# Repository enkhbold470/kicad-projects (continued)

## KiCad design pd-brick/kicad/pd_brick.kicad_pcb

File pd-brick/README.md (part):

# PD Brick

A USB-C Power Delivery bench supply: STUSB4500 sink, LM5176 buck-boost, 1.2-22 V set over I2C by an ESP32-S3.

| Layers | Size | Parts | Nets | Connections routed | Vias | ERC errors | DRC errors / unconnected / parity |
|---|---|---|---|---|---|---|---|
| 4 | 100 x 80 mm | 120 | 71 | 283 -> 0 open | 208 | 0 | 0 / 0 / 0 |

**Not fabricated, assembled or powered.** Every number on this page is measured by KiCad 10 on the files in this folder; the full measurements are in [`report.json`](report.json).

| | |
|---|---|
| KiCad project | [`kicad/`](kicad/) |
| Gerbers, BOM, CPL, STEP, schematic PDF | [`fab/`](fab/) |
| Renders | [top](media/top.png), [bottom](media/bottom.png) |
| Design process, every step as KiCad rendered it | [`media/design-process.mp4`](media/design-process.mp4) |

PD Brick is a USB-C Power Delivery programmable bench supply with a 1.2-22 V output. It was designed with the HeyPCB method on KiCad 10. A headless pipeline (KiCad 10.0.6, Freerouting 2.4.1) took the brief in `board.json` through schematic, placement, routing, pours, DRC and fab outputs.

**This board has not been fabricated, assembled or powered. There is no firmware.** On the final run it passes these checks:

- ERC and the netlist round trip;
- routing at 0 open;
- DRC with 0 errors, 0 unconnected and 0 schematic-parity rows;
- DFM with 0 errors.

The fab gate is ready. Everything under "Check before ordering" is a datasheet calculation or a layout measurement, not a bench result.

## What it is

- **Input:** USB-C, USB PD 3.0 sink up to 20 V (ST STUSB4500). The controller closes an AOD4185 P-FET between the receptacle and the power stage. There is a 24 V TVS on the receptacle.
- **Converter:** TI LM5176 4-switch buck-boost at about 390 kHz, with:
  - four TI CSD18563Q5A 60 V FETs;
  - a Coilcraft XAL7070 4.7 uH / 15.2 A inductor;
  - a 10 mOhm low-side current-sense resistor;
  - 220 uF + 4 x 10 uF on each side.

  The output is about 1.2-22 V.
- **Setpoint:** a Microchip MCP4725 12-bit I2C DAC injects into the LM5176 feedback node through 15k. A higher code gives a lower voltage.
- **Monitor:** a TI INA228 (20-bit V / I / power / energy) on a 10 mOhm high-side output shunt. It shares the LM5176's average-current-limit filter on the same shunt (50 mV, about 5 A).
- **Output enable:** one CSD18563Q5A high-side N-FET. Its gate is pulled up from a 25.6 V rail made by an MT3608 boost, Vgs is clamped at 12 V, and a 2N7002 pulls the gate down. The output is off from reset.
- **Output:** Phoenix MKDS 1,5/2-5,08 screw terminal (17.5 A), with an SMBJ24A TVS and 1 uF across it.
- **MCU:** ESP32-S3-WROOM-1-N8R8, from the HeyPCB block `esp32_s3_minimal`:
  - Wi-Fi for remote control;
  - native USB on the same USB-C port (USBLC6-2SC6 on D+/D-, referenced to 3V3);
  - BOOT and RESET buttons.
- **3.3 V:** Diodes AP63203 buck from VBUS (3.8-32 V in). An LDO would burn up to 8 W from a 20 V contract.
- **UI:**
  - a 1x4 0.1" header for a 1.3" I2C OLED (GND, VCC, SCL, SDA), with the bus pull-ups;
  - an Alps EC11E push-button encoder;
  - PWR, PD and OUT LEDs.
- **Board:** 100 x 80 mm, four M3 holes, 4 layers:
  - F.Cu;
  - In1, a GND plane;
  - In2, routing with a 3V3 pour;
  - B.Cu.

### Chip substitutions

| Asked for | Fitted | Why |
|---|---|---|
| TPS55289 (or similar) I2C buck-boost | LM5176 controller + 4 x CSD18563Q5A + MCP4725 DAC | KiCad 10 has no TPS55289 (or TPS552xx) symbol, and the live JLC lookup returned no TPS55289 row. The LM5176 (`Regulator_Switching:LM5176PWP`, LCSC C442493) has no I2C, so the DAC programs its FB node. |
| STUSB4500, AP33772 or CH224K | STUSB4500 | All three have KiCad 10 symbols. The AP33772 returned no JLC row. The CH224K is pin-strapped, with no I2C. The STUSB4500 (C2678061) renegotiates over I2C at 0x28. |
| INA228 (or INA226) | INA228 | `Sensor_Energy:INA228`, C2887910. |
| Load switch or MOSFET | one CSD18563Q5A high-side N-FET + MT3608 gate rail | No KiCad 10 load switch covers 1-22 V at several amps. A P-FET cannot turn on at a 1 V output. A low-side switch is bypassed by any second ground (a scope, or a USB-powered load). |
| (VBUS switch for VBUS_EN_SNK) | AOD4185 on the generic `Transistor_FET:Q_PMOS_GDS` symbol | KiCad 10 has no AOD4185 symbol. Q_PMOS_GDS (1 G, 2 D, 3 S) is this part's TO-252 land (tab = drain). |
| (power FETs) | CSD18563Q5A, 5 x 6 mm | The 3.3 x 3.3 mm CSD18543Q3A was tried first. Its KiCad VSON land puts the gate pad 0.14 mm from a source pad, so DRC fails at 0.2 mm on the footprint itself. |

### How it is wired

```
USB-C -VBUS-> AOD4185 (STUSB4500 VBUS_EN_SNK) -VIN-> LM5176 buck-boost -VOUT-> 10 mOhm shunt -VOUT_SH-> N-FET -OUT_P-> terminal
   |                                                ^ FB <- 15k <- MCP4725 (I2C)   |  ISNS 100R/100R/1uF -> LM5176 + INA228
   +-VBUS-> AP63203 -3V3-> ESP32-S3, STUSB4500 I2C side, INA228, DAC, OLED, encoder          gate <- 1M <- 25.6 V (MT3608 off VIN)
```

- **Setting the output.** FB has 100k from VOUT and 4.7k to GND, and the DAC drives FB through 15k:

  VOUT = 0.8 V x (1 + 100/4.7 + 100/15) - VDAC x 100/15

  That is about 23.2 V at code 0 and 1.2 V at full scale. Firmware clamps the code to 1.2-22 V.
- **Order at power-up.**
  1. The STUSB4500 closes the VBUS switch at attach.
  2. The LM5176 stays off: EN has a 100k pull-down.
  3. The output stays off: OUT_OFF has a 22k pull-up.
  4. Firmware writes the DAC, sets BB_EN high, then pulls OUT_OFF low.
- **Wide power nets.** No 1.2 mm power track lands on an IC pin. On the routed board, the seven power-path nets reach only FETs, the inductor, passives, the TVS, the zener and the terminal. Every IC pin on a power net hangs off it through a resistor, placed at the power node (an `at` target in the brief):
  - LM5176 VIN, VISNS, VOSNS, SW1/SW2, CS/CSG and ISNS;
  - STUSB4500 VDD;
  - INA228 VBUS;
  - MT3608 IN.
- **I2C** (IO38 SDA, IO39 SCL, 4.7k pull-ups):
  - STUSB4500 at 0x28;
  - INA228 at 0x40;
  - MCP4725 at 0x60;
  - the OLED module at its own address.
- **ESP32-S3 pins.** All GPIOs are on the module's right column and bottom row, which face the board:

  | Pin | Function |
  |---|---|
  | IO42 / IO41 / IO40 | encoder A / B / switch |
  | IO1 / IO2 | PD / OUT LEDs |
  | IO10 | PD_RST |
  | IO11 | PD_ALERT |
  | IO12 | BB_EN |
  | IO14 | OUT_OFF |
  | IO19 / IO20 | USB D- / D+ |
  | IO0 | BOOT |

  The LM5176 PGOOD, the INA228 ALERT and a VIN divider were cut to shorten routing; the INA228 and STUSB4500 report the same information over I2C.

## Measured (full run of 2026-10-01)

Gate numbers come from `report.json`. Rows marked "on the board" were measured on `kicad/pd_brick.kicad_pcb` with KiCad's Python (`pcbnew`, read-only scripts). Current ratings use `ipc2221_amps` from the pipeline (IPC-2221, 1 oz outer, 0.5 oz inner). A path's rating is the total current at which its busiest segment reaches its own rating at a 20 C rise. The share each segment carries comes from solving the net's copper as a resistor network, with the source pads tied (ideal contacts).

| Gate | Result |
|---|---|
| Composition | 18 block instances, 16 distinct blocks (11 written for this board, 5 reused) → 120 footprints, 71 nets |
| Part binding | 116 of 116 BOM parts bound to a pinned LCSC table, 0 unsourced, 0 conflicts. H1-H4 are drilled M3 holes, kept out of the BOM. 23 distinct Extended parts, about $69 in JLC loading fees. 1 warning: the 10k 0603 R9 (C25804, the ESP32 EN pull-up) had 0 stock at its 2026-06-23 snapshot |
| ERC (`kicad-cli sch erc --severity-all`) | 0 errors, 0 warnings |
| Netlist round trip | identical, 71 nets |
| Freerouting, rung 1, fanout on (kept) | 283 → **0 open** in 160.9 s, with no last-mile help. DRC score 0, 73 vias |
| Freerouting, rung 1, fanout off (for comparison) | 283 → 1 open (VOUT, R17.1 to C29.1) in 38.4 s. The last-mile router found no path, so this rung was not kept |
| Copper | 908 tracks, 73 routing vias, 2856.2 mm of track (F.Cu 1624.4, In2 1030.5, B.Cu 201.3). No segment was widened, kept narrow or raised: every segment is at its class width (also checked on the board) |
| VBUS input (on the board) | 0.6 mm, all on F.Cu, no vias. Each receptacle VBUS pad pair has its own track to Q1's source pad: 8.6 mm from A4/B9 and 7.5 mm from A9/B4. No segment is shared; the two tracks meet only inside the source pad. They split the current 45 / 55. Path rating **4.07 A** at a 20 C rise (3.0 A at 10 C) |
| Power path (on the board) | VIN, BB_SW1, BB_SW2, BB_CS, VOUT, VOUT_SH and OUT_P run only on F.Cu at 1.2 mm, with no vias and no necks. OUT_P's branch to the output TVS is F.Cu too. VIN from Q1 to the buck high-side FET, and the output path (VOUT, VOUT_SH, OUT_P) to the terminal, each rate **3.70 A** at a 20 C rise |
| 3.3 V buck (on the board) | Switch node 0.8 mm on F.Cu, no vias: 1.6 mm from the AP63203's SW pin to the inductor pad, 5.1 mm with the branch to the bootstrap cap. Rated **2.76 A** at a 20 C rise. 3V3 is 0.3 mm everywhere (271.5 mm: F.Cu 87.9, In2 169.1, B.Cu 14.5, 10 vias), with the In2 3V3 pour around it |
| Pours (only after a measured 0 open) | GND on F.Cu, B.Cu and In1; 3V3 on In2. 144 stitching vias, 0 island-repair vias, still 0 open. 217 vias in all |
| DRC (`kicad-cli pcb drc --severity-all --schematic-parity`) | fresh: 0 errors, 3 warnings, 0 unconnected, 0 parity |
| DFM (`jlcpcb_4layer`) | 0 errors, 1 warning: 338 stock-footprint silk strokes at 0.12 mm, which the fab prints at its 0.15 mm minimum |
| Fab gate | **ready**, no blockers. Outputs: gerbers for four copper layers (the gerber job says 4 layers, 1.6 mm), drill, BOM, JLC placement file (8 rotations corrected), position file, schematic PDF, STEP |

- **The 3 DRC warnings** are `lib_footprint_mismatch` on three parts: the USB-C receptacle (J1), the terminal (J2) and the ESP32-S3 module (U4).
  - Silk is clipped at the board edge, so each has fewer silk shapes than its library copy: 2 of 5, 6 of 9 and 4 of 8 (on the board).
  - J1's shield pads are also set to join the GND pour solid.
- **Hole spacing.** The closest via holes on different nets are 0.53 mm apart (I2C_SCL and J1_PD_DISCH), against the 0.5 mm board rule (on the board).
- **Silk** (from `report.json`, texts read back on the board).
  - All 7 words fit: PD IN, PWR, PD, OUT, BOOT, RST and SET.
  - OUT+ and OUT- sit beside the terminal's two pins.
  - The OLED header's pin names (GND, VCC, SCL, SDA) are printed on both faces: 8 labels.
  - All 4 back title lines fit.
  - 84 designators were seated and 28 hidden; parts that carry a word hide theirs. 10 silk shapes were clipped at the board edge, and 9 stitching vias gave way to text.
- **Media.** Render and video ran in the same full run as the gates. The design-process video (`media/design-process.mp4`) is 168.6 s long (ffprobe on the run's own MP4), made from 253 stills. It ends on the fab card.
- **Repeatability.** Two full runs of the final brief (one `--no-media`, then the full run with media) routed identically: 908 tracks, 73 vias, 2856.2 mm, and the same VBUS feeds and split. A brief change is a new sample, though. Adding one more F.Cu keep-out (under the receptacle body) routed the VBUS feeds into one shared 0.6 mm track again (see below). After the final run, only `why` texts in `board.json` were corrected; nothing they feed changed.

### What changed along the way (each measured on this board)

- **The schematic packer.** It could not fit one 52-part buck-boost block on A1 (993 mm wide), so the block was split into a controller block and a power-stage block.
- **Sense resistors at the power nodes.** Left to the shelf placer, they landed under the controller. Every 1.5 mm power track then had to cross the controller's satellites, and Freerouting stalled at 22 unrouted.
- **The output switch.** A back-to-back (source-to-source) pair was tried first. With the S-S-S-G pinout, one gate always sits across the wide source-to-source track, and that gate net was left open in four of six rebuilds. The board now uses a single FET (see "Check before ordering").
- **An early 0-open route** ran the output (OUT_P) through one via and 17.9 mm of In2: about 1.3 A on 0.5 oz inner copper. Placing the terminal pin level with the FET drain moved it to F.Cu. On the final board, OUT_P has no inner-layer copper at all.
- **The VBUS input.** On the previous build, the last 7.8 mm of VBUS into Q1 was a single 0.6 mm track carrying all the input current. That is 2.24 A at a 20 C rise, and about a 39 C rise at 3 A. Freerouting had left the A9/B4 pad pair unrouted because its CC2 fan-out via sat too close to that pad's exit. The last-mile router then joined that pair onto the other pair's track. A wider class cannot help: the receptacle's VBUS pads are 0.6 mm wide, 0.2 mm from the GND pad beside them, and Freerouting runs with neckdown off. What fixed it, over four `--no-media` runs:
  - Q1 is locked with its source pad level with the middle of the two VBUS pad pairs, and its gate network is pinned above it, out of the way.
  - The VBUS class clearance went from 0.2 mm to 0.15 mm, the board's. At 0.2 mm, a 0.6 mm track had a 0.05 mm window to leave the A4/B9 pad, and Freerouting reported `J1-B9 -> J1-A9` unrouted.
  - `board.keepouts` add:
    - an F.Cu track ban above the A4/B9 feed and a via ban along it;
    - an F.Cu track ban box and wedge between the two feeds, up to the source pad;
    - a via guard beside the CC2 pad.
  - The first try used via-free corridors along both feeds. Both pairs still merged into one 6.2 mm detour. The width floor also kept two 0.45 mm VBUS stubs that Freerouting laid at the pads narrow, because it never widens a segment whose midpoint lies in a via keep-out.
- **The 3.3 V buck.** Before, the switch node was a 0.15 mm track (about 0.8 A), and the output caps sat on the far side of the IC from the inductor. Now the IC, inductor and four caps are locked as one cell:
  - the input cap sits under the IN and GND pins;
  - the inductor sits against the SW pin;
  - the bootstrap cap sits above BST;
  - both output caps sit under the inductor's 3V3 pad, with their GND pads beside the input cap's.

  The switch node has its own 0.8 mm class and 3V3 a 0.3 mm class.
- **Silk.** On the previous build, 4 of 7 words fit (BOOT, RST and the OUT LED's word did not), the terminal had no + / - mark, and 0 of 8 OLED pin labels fit. The fixes were all in the brief:
  - **BOOT and RESET.** The module's courtyard box, antenna keep-out included, spans x -4 to 44 mm and y down to 20.3 mm. The silk stage keeps words off every courtyard box, so the two buttons moved out of it.
  - **LEDs.** They are spaced 3.75 mm apart, each with its resistor below it.
  - **OLED header.** It now stands vertical, so its pin names land beside the pins.
  - **Terminal marks.** They come from a `silk.switches` entry. `silk.polarity` tries spots 1.9-2.3 mm from each pin, and every one of them hits the terminal's own 2.6 mm pads or its body outline.
- **Rules.**
  - The power class went from 1.5 mm to 1.2 mm.
  - Default track and clearance went from 0.2 mm to 0.15 mm.
  - Default vias went from 0.6/0.3 to 0.45/0.2 mm.

  All are inside the DFM profile.

## Check before ordering

### Current

- **The input is the limit, not the converter.** Output power can never exceed the USB PD contract, less conversion loss.
  - 20 V / 3 A (60 W) gives roughly 50-55 W out.
  - A 5 V-only source gives about 13 W.
- **Out of the box, the STUSB4500 asks for only 20 V / 1 A**, then 15 V / 1.5 A, then 5 V (default NVM, datasheet DS12499 Table 18). That is a 20 W ceiling. Firmware must rewrite the PDO currents over I2C and renegotiate before drawing more.
- **The USB-C receptacle.** The HRO TYPE-C-31-M-12 drawing rates the contact set 5 A / 20 V. Above 3 A, USB PD also needs a 5 A e-marked cable and a source that offers it.
- **The VBUS input is rated for a 3 A contract, with two 0.6 mm feeds in parallel.**
  - Each receptacle VBUS pad pair has its own 0.6 mm F.Cu track to Q1's source pad: 8.6 mm from A4/B9 and 7.5 mm from A9/B4. There are no vias and no shared segment (measured above).
  - With the copper alone deciding, the shorter feed takes 55%. At 3 A that is 1.65 A on a 0.6 mm track, about a 10 C rise. The other feed takes 1.35 A, about 6 C. The pair is rated 4.07 A at a 20 C rise, and 3.0 A at 10 C.
  - **What is left:**
    - 0.6 mm is the narrowest point, and it is set by the receptacle. Its VBUS pads are themselves 0.6 mm wide, and no wider track can enter them.
    - The split assumes the plug shares current between the two pad pairs as the copper does. If contact resistance pushed everything through one pair, a single 0.6 mm track is 2.24 A at a 20 C rise.
    - It is not sized for a 5 A contract.
  - After Q1, VIN is 1.2 mm on F.Cu to the buck-boost: 3.70 A at a 20 C rise.
- **Output current the copper supports: about 3.5 A.** The ratings below use IPC-2221 (I = k x dT^0.44 x A^0.725) on 1 oz outer copper.
  - The load path is 1.2 mm on F.Cu end to end (measured above). That is about 2.7 A at a 10 C rise and 3.7 A at 20 C. The power class's own 3.5 A budget is about an 18 C rise.
  - The LM5176's hardware average-current limit (4.3-5.7 A, below) is higher than that. At 5 A the formula gives about a 40 C rise on these tracks. Hold the output at 3.5 A or less in firmware, using the INA228.
  - In boost mode the inductor tracks (BB_SW1, BB_SW2, BB_CS) carry the input current instead, which the PD contract caps.
- **Inner layers carry no load current.** On the final board, none of VBUS, VIN, BB_SW1, BB_SW2, BB_CS, VOUT, VOUT_SH or OUT_P has inner-layer copper or a via.
- **The GND return** relies on the pours and stitching vias, not on the 0.15 mm routed GND tracks.
- **3.3 V rail.**
  - The AP63203's switch node is 0.8 mm on F.Cu, 1.6 mm from the SW pin to the inductor pad. It is rated 2.76 A at a 20 C rise, against the regulator's 2 A (about a 10 C rise at 2 A).
  - The input cap's VBUS pad is 1.6 mm of 0.6 mm track from the IN pin. Its GND pad sits under the IC's GND pin. The F.Cu GND pour joins the IC's GND pin, that pad and both output caps' GND pads along straight lines (on the board).
  - The output caps are 3.2 and 5.2 mm of 0.3 mm track from the inductor's 3V3 pad (pad centre to pad centre).
  - The 3V3 rail is 0.3 mm everywhere: about 1.4 A at a 20 C rise on F.Cu. From the inductor to the module's 3V3 pin it runs 30.1 mm (15.9 mm F.Cu, 14.2 mm In2 inside the In2 3V3 pour, 2 vias).
  - The bootstrap trace is a default 0.15 mm track, 2.2 mm long.
- **Hardware current limits.**
  - The LM5176 ISNS loop limits the average output current at 50 mV (43-57) across the 10 mOhm shunt: 4.3-5.7 A. It is a slow loop acting through soft-start, not a programmable bench constant-current mode. A real CC mode needs firmware on the INA228.
  - The cycle-by-cycle limits over the 10 mOhm sense resistor are 80 mV valley (buck) and 120 mV, 140 mV maximum, peak (boost): 8 A and 12-14 A of inductor current. The XAL7070-472 saturates at 15.2 A.
- **No reverse blocking at the output.** The single N-FET's body diode conducts from the terminal into the converter's output capacitors when an external source sits above the set voltage. Do not leave a battery on the terminal while the supply is off or set lower.

### Thermal

- **LM5176 VCC regulator.** BIAS is grounded here; the datasheet doesn't say how to tie an unused BIAS, so confirm with TI. Gate drive is roughly 2-4 FETs x 15 nC x 390 kHz, 12-23 mA, all drawn from VIN through the internal regulator: up to about 0.3 W in the controller at a 20 V contract.
- **FETs.** CSD18563Q5A is 5.7 mOhm at Vgs 10 V (JLC listing).
  - The LM5176 drives about 7.35 V of gate. At a 5 V contract VCC follows VIN, which gives about 4.9 V of gate drive.
  - At 4 A each conducting FET dissipates roughly 0.1-0.15 W plus switching loss.
  - The drain pads sit on F.Cu inside the GND pours, with no vias under them. None of the power-path nets has a via (on the board).
- **Inductor.** XAL7070-472MEC, 14.26 mOhm DCR (JLC listing): about 0.23 W at 4 A.
- **Shunts.** Two 10 mOhm 1 W 1206 parts: 0.16 W each at 4 A DC.
- **Output switch at high output voltage.** The gate rail is 25.6 V, so Vgs is only about 3.6 V at 22 V out, well short of the 10 V Rds(on) condition. For full current, keep the output at or below about 20 V (5.6 V Vgs), or raise the MT3608 rail (28 V maximum).
- **Bulk capacitors.** The two 220 uF 50 V electrolytics (MA50V220M10x10) came from a live JLC lookup that gives no ESR or ripple-current rating. Check them against about 2 A RMS on the input side at full load.

### Layout and design items to verify

- **Gate-drive and feedback lengths.** The controller sits below the power stage. Measured on the board, pin to pin:
  - high-side gates: BB_HDRV1 is 31.8 mm (29.1 mm on In2, 2 vias), and BB_HDRV2 is 29.0 mm (25.2 mm on In2, 2 vias);
  - low-side gates: BB_LDRV1 is 20.5 mm (14.0 mm on In2, 2 vias), and BB_LDRV2 is 23.5 mm, all on F.Cu;
  - the FB node runs 41.6 mm from the top divider resistor at the output caps (R17) to the IC. 33.0 mm of that is on In2, through 2 vias.

  Both work against switching performance and noise. A hand-tuned layout would put the controller beside the FETs.
- **Output TVS.** D6 reaches the terminal pin through 10.0 mm of F.Cu, with no via. A TVS clamps best right at the terminal. The 1 uF (C38) is 4.2 mm away on F.Cu.
- **VBUS under the receptacle.** The 3.3 V buck's VBUS feed runs on F.Cu under the USB-C receptacle's body (a straight 11.4 mm along x = 4.67 mm), with only solder mask between it and the receptacle's GND shell. It carries only the buck's input current. A brief keep-out there was tried, and it merged the two main VBUS feeds into one shared 0.6 mm track again (2.24 A), so it was dropped. Check the receptacle's seating, or move that feed by hand, before ordering.
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
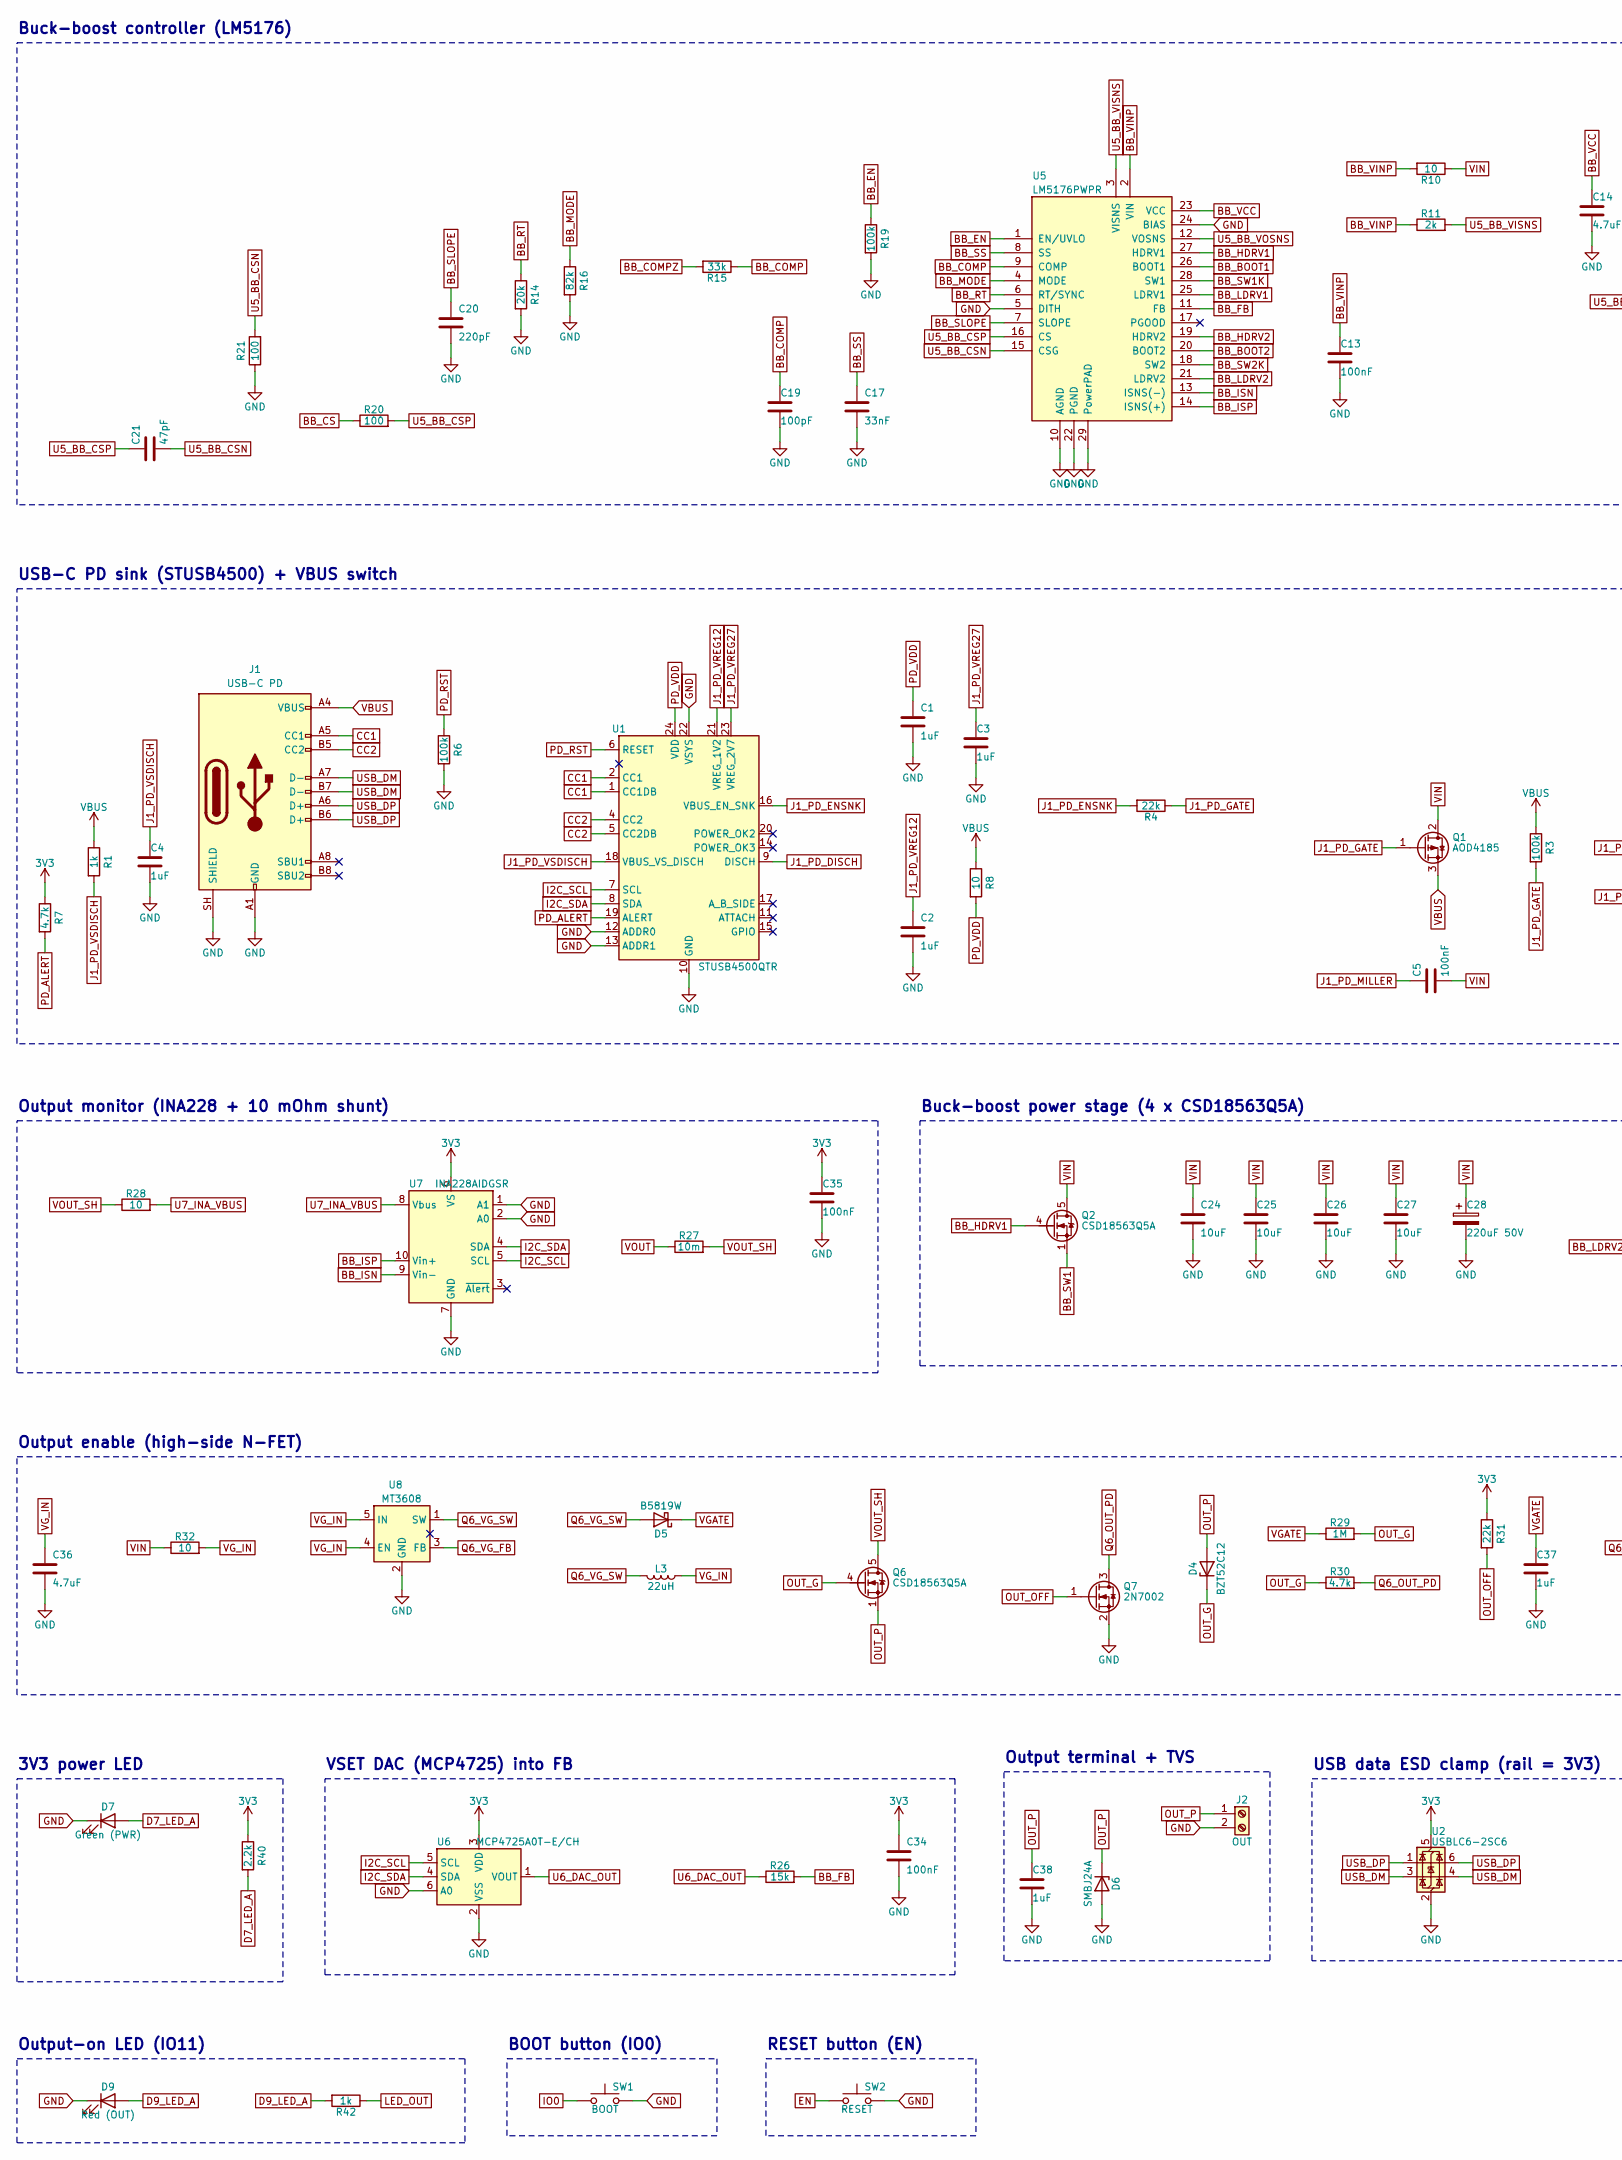
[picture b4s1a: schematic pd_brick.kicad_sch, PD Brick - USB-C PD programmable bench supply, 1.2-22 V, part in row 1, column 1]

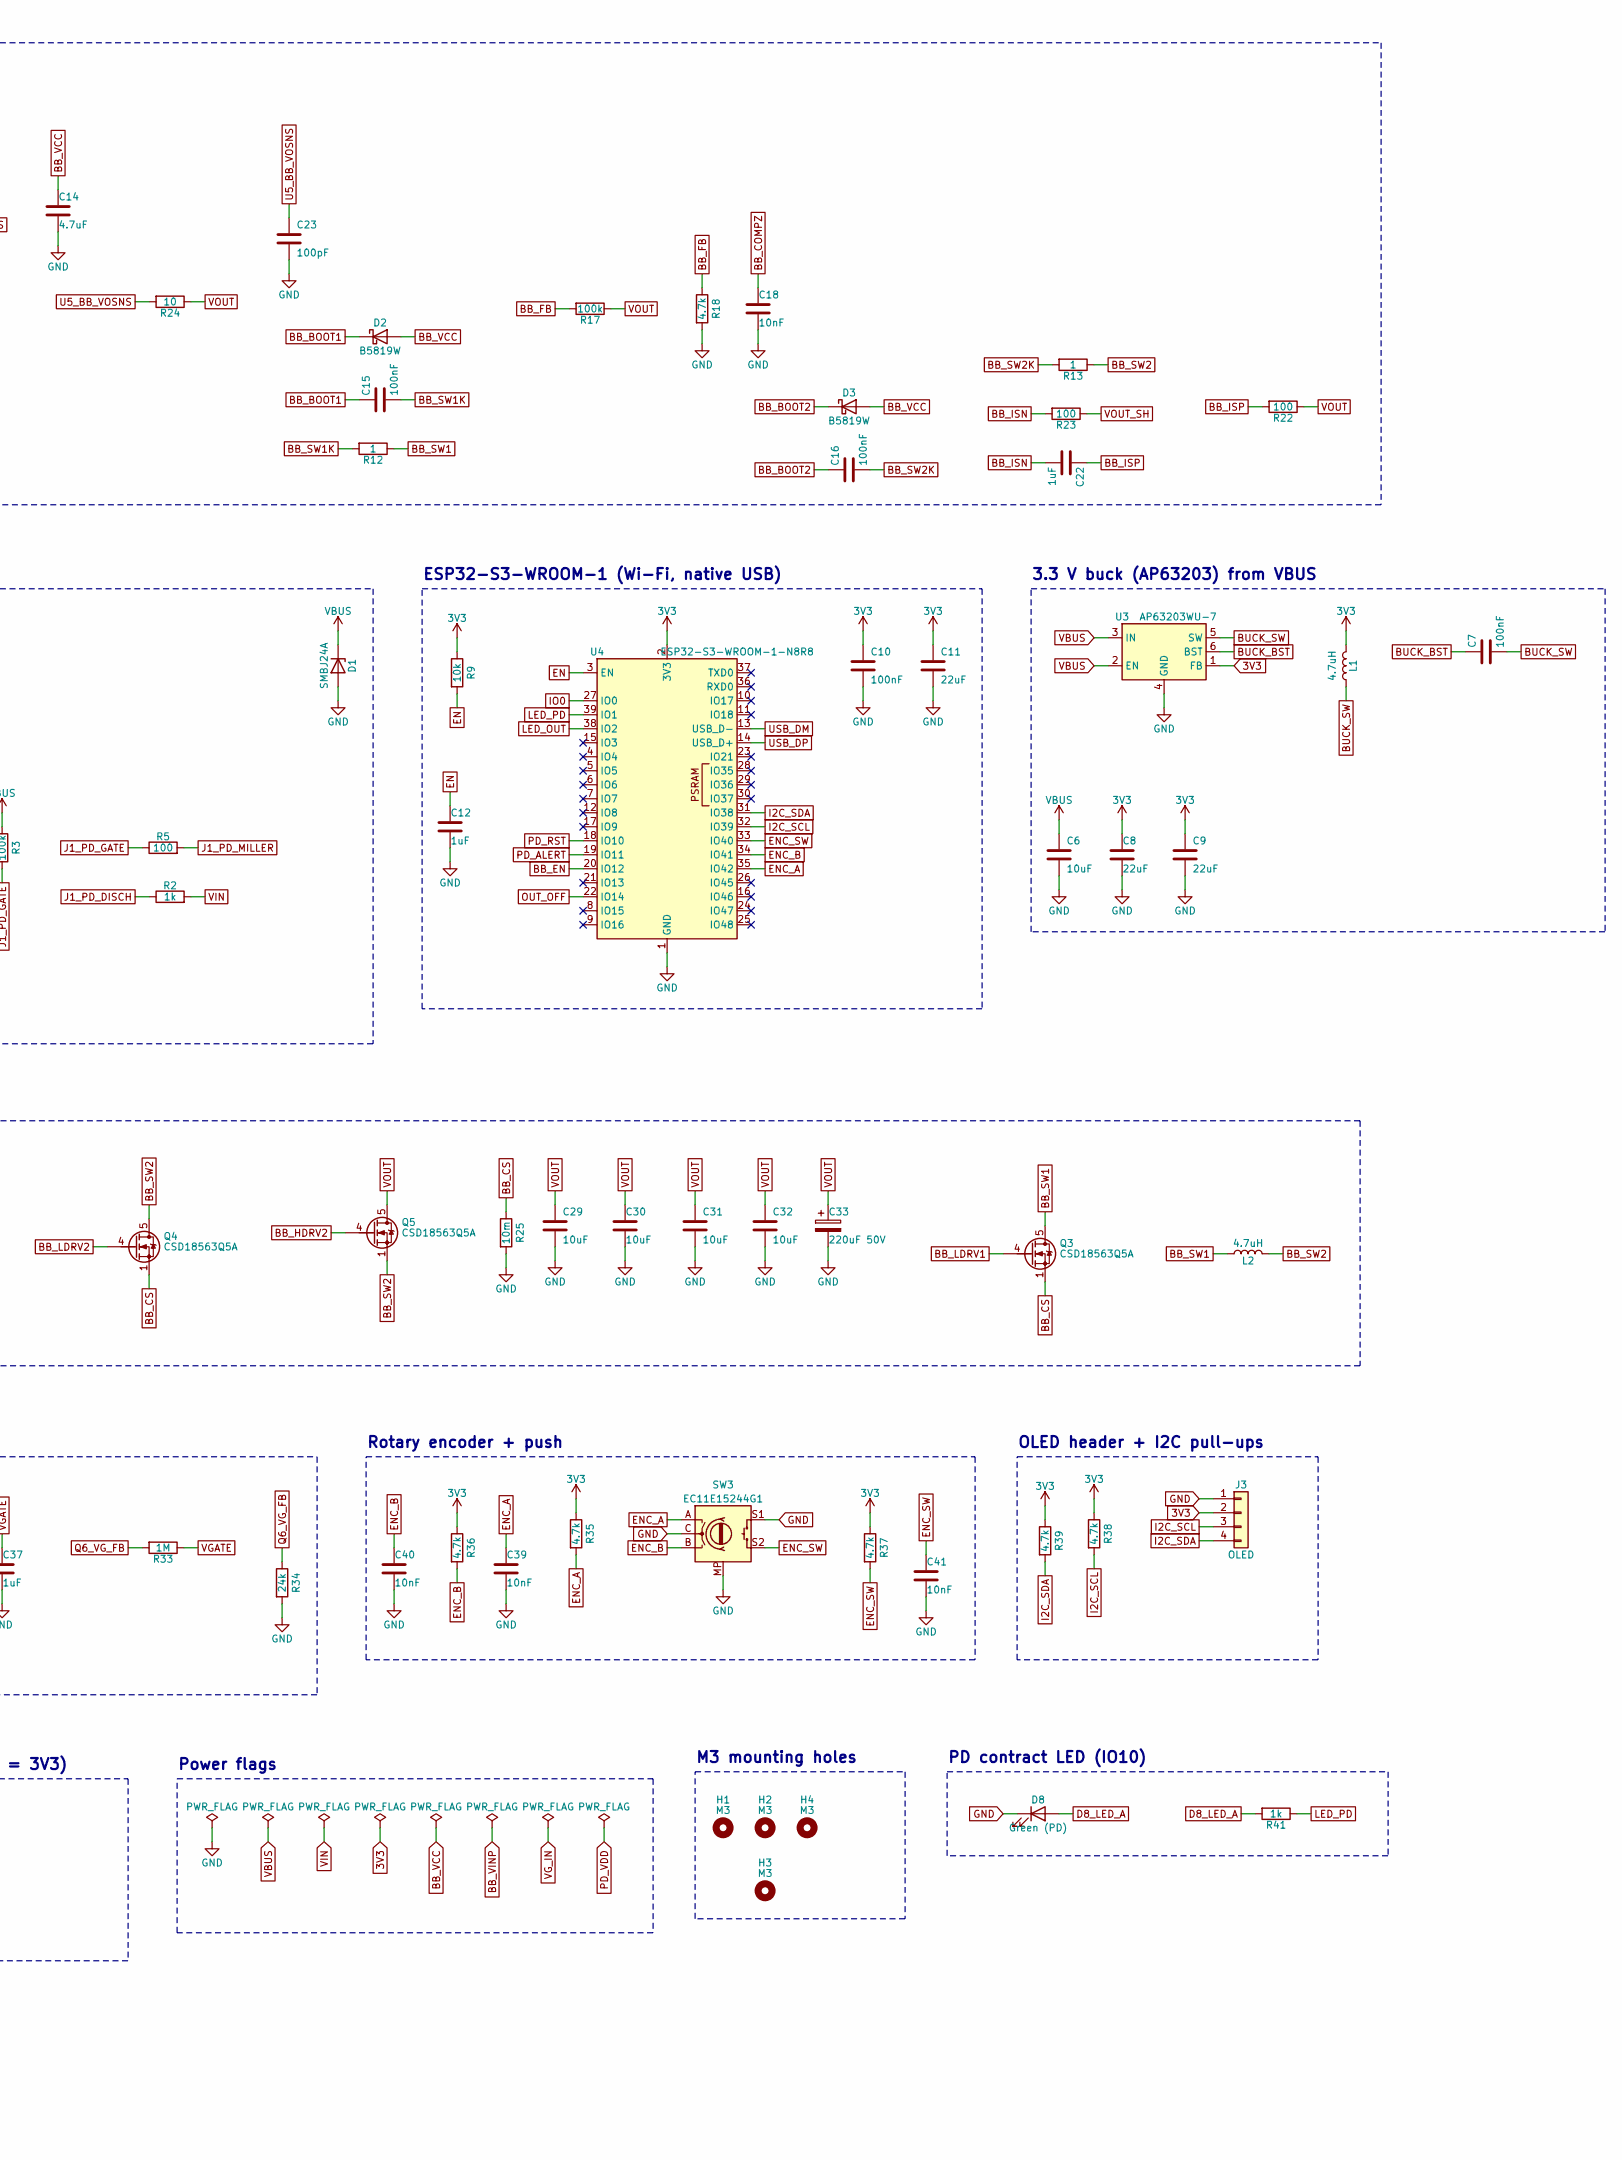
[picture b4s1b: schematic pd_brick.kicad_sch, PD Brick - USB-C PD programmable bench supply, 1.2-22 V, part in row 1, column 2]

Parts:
C1, C2, C3, C4, C12, C22: 1uF; C_0603_1608Metric; MPN CL10A105KB8NNNC; LCSC C15849
C5, C7, C10, C13, C15, C16, C34, C35: 100nF; C_0603_1608Metric; MPN CC0603KRX7R9BB104; LCSC C14663
C6, C24, C25, C26, C27, C29, C30, C31, C32: 10uF; C_1206_3216Metric; MPN CL31A106KBHNNNE; LCSC C13585
C8, C9, C11: 22uF; C_0805_2012Metric; MPN CL21A226MAQNNNE; LCSC C45783
C14: 4.7uF; C_0805_2012Metric; MPN CL21A475KAQNNNE; LCSC C1779
C17: 33nF; C_0603_1608Metric; MPN CL10B333KB8NNNC; LCSC C21117
C18, C39, C40, C41: 10nF; C_0603_1608Metric; MPN 0603B103K500NT; LCSC C57112
C19, C23: 100pF; C_0603_1608Metric; MPN CL10C101JB8NNNC; LCSC C14858
C20: 220pF; C_0603_1608Metric; MPN CL10B221KB8NNNC; LCSC C1603
C21: 47pF; C_0603_1608Metric; MPN CL10C470JB8NNNC; LCSC C1671
C28, C33: 220uF 50V; CP_Elec_10x10; MPN MA50V220M10x10; LCSC C46550473
C36: 4.7uF; C_1206_3216Metric; MPN 1206B475K500NT; LCSC C29823
C37, C38: 1uF; C_0805_2012Metric; MPN CL21B105KBFNNNE; LCSC C28323
D1, D6: SMBJ24A; D_SMB; MPN SMBJ24A; LCSC C123819
D2, D3, D5: B5819W; D_SOD-123; MPN B5819W SL; LCSC C8598
D4: BZT52C12; D_SOD-123; MPN BZT52C12; LCSC C173429
D7: Green (PWR); LED_0603_1608Metric; MPN KT-0603G; LCSC C12624
D8: Green (PD); LED_0603_1608Metric; MPN KT-0603G; LCSC C12624
D9: Red (OUT); LED_0603_1608Metric; MPN KT-0603R; LCSC C2286
H1, H2, H3, H4: M3; MountingHole_3.2mm_M3
J1: USB-C PD; USB_C_Receptacle_HRO_TYPE-C-31-M-12; MPN TYPE-C-31-M-12; LCSC C165948
J2: OUT; TerminalBlock_Phoenix_MKDS-1,5-2-5.08_1x02_P5.08mm_Horizont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; MPN MKDS 1,5/ 2-5,08; LCSC C5183929
J3: OLED; PinHeader_1x04_P2.54mm_Vertical; MPN PZ254V-11-04P; LCSC C2691448
L1: 4.7uH; L_Sunlord_SWPA4030S; MPN SWPA4030S4R7MT; LCSC C57269
L2: 4.7uH; L_Coilcraft_XAL7070-XXX; MPN XAL7070-472MEC; LCSC C3911513
L3: 22uH; L_Changjiang_FNR4030S; MPN FNR4030S220MT; LCSC C167883
Q1: AOD4185; TO-252-2; MPN AOD4185; LCSC C400894
Q2, Q3, Q4, Q5, Q6: CSD18563Q5A; TDSON-8-1; MPN CSD18563Q5A; LCSC C77239
Q7: 2N7002; SOT-23; MPN 2N7002; LCSC C8545
R1, R41, R42: 1k; R_0603_1608Metric; MPN 0603WAF1001T5E; LCSC C21190
R2: 1k; R_1206_3216Metric; MPN 1206W4F1001T5E; LCSC C4410
R3, R6, R17, R19: 100k; R_0603_1608Metric; MPN 0603WAF1003T5E; LCSC C25803
R4, R31: 22k; R_0603_1608Metric; MPN 0603WAF2202T5E; LCSC C31850
R5, R20, R21, R22, R23: 100; R_0603_1608Metric; MPN 0603WAF1000T5E; LCSC C22775
R7, R18, R30, R35, R36, R37, R38, R39: 4.7k; R_0603_1608Metric; MPN 0603WAF4701T5E; LCSC C23162
R8, R10, R24, R28, R32: 10; R_0603_1608Metric; MPN 0603WAF100JT5E; LCSC C22859
R9: 10k; R_0603_1608Metric; MPN 0603WAF1002T5E; LCSC C25804
R11: 2k; R_0603_1608Metric; MPN 0603WAF2001T5E; LCSC C22975
R12, R13: 1; R_0603_1608Metric; MPN 0603WAF100KT5E; LCSC C22936
R14: 20k; R_0603_1608Metric; MPN 0603WAF2002T5E; LCSC C4184
R15: 33k; R_0603_1608Metric; MPN 0603WAF3302T5E; LCSC C4216
R16: 82k; R_0603_1608Metric; MPN 0603WAF8202T5E; LCSC C23254
R25, R27: 10m; R_1206_3216Metric; MPN FMF06FTHR010-LH; LCSC C105362
R26: 15k; R_0603_1608Metric; MPN 0603WAF1502T5E; LCSC C22809
R29, R33: 1M; R_0603_1608Metric; MPN 0603WAF1004T5E; LCSC C22935
R34: 24k; R_0603_1608Metric; MPN 0603WAF2402T5E; LCSC C23352
R40: 2.2k; R_0603_1608Metric; MPN 0603WAF2201T5E; LCSC C4190
SW1: BOOT; SW_SPST_PTS810; MPN PTS810SJM250SMTRLFS; LCSC C116501
SW2: RESET; SW_SPST_PTS810; MPN PTS810SJM250SMTRLFS; LCSC C116501
SW3: EC11E15244G1; RotaryEncoder_Alps_EC11E-Switch_Vertical_H20mm; MPN EC11E15244G1; LCSC C370970
U1: STUSB4500QTR; QFN-24-1EP_4x4mm_P0.5mm_EP2.7x2.7mm; MPN STUSB4500QTR; LCSC C2678061
U2: USBLC6-2SC6; SOT-23-6; MPN USBLC6-2SC6; LCSC C7519
U3: AP63203WU-7; TSOT-23-6; MPN AP63203WU-7; LCSC C780769
U4: ESP32-S3-WROOM-1-N8R8; ESP32-S3-WROOM-1; MPN ESP32-S3-WROOM-1-N8R8; LCSC C2913201
U5: LM5176PWPR; HTSSOP-28-1EP_4.4x9.7mm_P0.65mm_EP3.4x9.5mm_ThermalVias; MPN LM5176PWPR; LCSC C442493
U6: MCP4725A0T-E/CH; SOT-23-6; MPN MCP4725A0T-E/CH; LCSC C144198
U7: INA228AIDGSR; TSSOP-10_3x3mm_P0.5mm; MPN INA228AIDGSR; LCSC C2887910
U8: MT3608; SOT-23-6; MPN MT3608; LCSC C84817

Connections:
3V3: C8.1, C9.1, C10.1, C11.1, C34.1, C35.1, J3.2, L1.2, R7.1, R9.1, R31.1, R35.1, R36.1, R37.1, R38.1, R39.1, R40.1, U2.5 (VBUS), U3.1 (FB), U4.2 (3V3), U6.3 (VDD), U7.6 (VS)
BB_BOOT1: C15.1, D2.1 (K), U5.26 (BOOT1)
BB_BOOT2: C16.1, D3.1 (K), U5.20 (BOOT2)
BB_COMP: C19.1, R15.1, U5.9 (COMP)
BB_COMPZ: C18.1, R15.2
BB_CS: Q3.1 (S), Q3.2 (S), Q3.3 (S), Q4.1 (S), Q4.2 (S), Q4.3 (S), R20.1, R25.1
BB_EN: R19.1, U4.20 (IO12), U5.1 (EN/UVLO)
BB_FB: R17.2, R18.1, R26.2, U5.11 (FB)
BB_HDRV1: Q2.4 (G), U5.27 (HDRV1)
BB_HDRV2: Q5.4 (G), U5.19 (HDRV2)
BB_ISN: C22.2, R23.2, U5.13 (ISNS(-)), U7.9 (Vin-)
BB_ISP: C22.1, R22.2, U5.14 (ISNS(+)), U7.10 (Vin+)
BB_LDRV1: Q3.4 (G), U5.25 (LDRV1)
BB_LDRV2: Q4.4 (G), U5.21 (LDRV2)
BB_MODE: R16.1, U5.4 (MODE)
BB_RT: R14.1, U5.6 (RT/SYNC)
BB_SLOPE: C20.1, U5.7 (SLOPE)
BB_SS: C17.1, U5.8 (SS)
BB_SW1: L2.1, Q2.1 (S), Q2.2 (S), Q2.3 (S), Q3.5 (D), R12.1
BB_SW1K: C15.2, R12.2, U5.28 (SW1)
BB_SW2: L2.2, Q4.5 (D), Q5.1 (S), Q5.2 (S), Q5.3 (S), R13.1
BB_SW2K: C16.2, R13.2, U5.18 (SW2)
BB_VCC: C14.1, D2.2 (A), D3.2 (A), U5.23 (VCC)
BB_VINP: C13.1, R10.2, R11.1, U5.2 (VIN)
BUCK_BST: C7.1, U3.6 (BST)
BUCK_SW: C7.2, L1.1, U3.5 (SW)
CC1: J1.A5 (CC1), U1.1 (CC1DB), U1.2 (CC1)
CC2: J1.B5 (CC2), U1.4 (CC2), U1.5 (CC2DB)
D7_LED_A: D7.2 (A), R40.2
D8_LED_A: D8.2 (A), R41.2
D9_LED_A: D9.2 (A), R42.2
EN: C12.1, R9.2, SW2.1, U4.3 (EN)
ENC_A: C39.1, R35.2, SW3.A, U4.35 (IO42)
ENC_B: C40.1, R36.2, SW3.B, U4.34 (IO41)
ENC_SW: C41.1, R37.2, SW3.S2, U4.33 (IO40)
GND: C1.2, C2.2, C3.2, C4.2, C6.2, C8.2, C9.2, C10.2, C11.2, C12.2, C13.2, C14.2, C17.2, C18.2, C19.2, C20.2, C23.2, C24.2, C25.2, C26.2, C27.2, C28.2, C29.2, C30.2, C31.2, C32.2, C33.2, C34.2, C35.2, C36.2, C37.2, C38.2, C39.2, C40.2, C41.2, D1.2 (A), D6.2 (A), D7.1 (K), D8.1 (K), D9.1 (K), J1.A1 (GND), J1.A12 (GND), J1.B1 (GND), J1.B12 (GND), J1.SH (SHIELD), J2.2, J3.1, Q7.2 (S), R6.2, R14.2, R16.2, R18.2, R19.2, R21.1, R25.2, R34.2, SW1.2, SW2.2, SW3.C, SW3.MP, SW3.S1, U1.10 (GND), U1.12 (ADDR0), U1.13 (ADDR1), U1.22 (VSYS), U1.25 (GND), U2.2 (GND), U3.4 (GND), U4.1 (GND), U4.40 (GND), U4.41 (GND), U5.5 (DITH), U5.10 (AGND), U5.22 (PGND), U5.24 (BIAS), U5.29 (PowerPAD), U6.2 (VSS), U6.6 (A0), U7.1 (A1), U7.2 (A0), U7.7 (GND), U8.2 (GND)
I2C_SCL: J3.3, R38.2, U1.7 (SCL), U4.32 (IO39), U6.5 (SCL), U7.5 (SCL)
I2C_SDA: J3.4, R39.2, U1.8 (SDA), U4.31 (IO38), U6.4 (SDA), U7.4 (SDA)
IO0: SW1.1, U4.27 (IO0)
J1_PD_DISCH: R2.1, U1.9 (DISCH)
J1_PD_ENSNK: R4.2, U1.16 (VBUS_EN_SNK)
J1_PD_GATE: Q1.1 (G), R3.2, R4.1, R5.1
J1_PD_MILLER: C5.1, R5.2
J1_PD_VREG12: C2.1, U1.21 (VREG_1V2)
J1_PD_VREG27: C3.1, U1.23 (VREG_2V7)
J1_PD_VSDISCH: C4.1, R1.2, U1.18 (VBUS_VS_DISCH)
LED_OUT: R42.1, U4.38 (IO2)
LED_PD: R41.1, U4.39 (IO1)
OUT_G: D4.1 (K), Q6.4 (G), R29.2, R30.1
OUT_OFF: Q7.1 (G), R31.2, U4.22 (IO14)
OUT_P: C38.1, D4.2 (A), D6.1 (K), J2.1, Q6.1 (S), Q6.2 (S), Q6.3 (S)
PD_ALERT: R7.2, U1.19 (ALERT), U4.19 (IO11)
PD_RST: R6.1, U1.6 (RESET), U4.18 (IO10)
PD_VDD: C1.1, R8.2, U1.24 (VDD)
Q6_OUT_PD: Q7.3 (D), R30.2
Q6_VG_FB: R33.2, R34.1, U8.3 (FB)
Q6_VG_SW: D5.2 (A), L3.2, U8.1 (SW)
U5_BB_CSN: C21.2, R21.2, U5.15 (CSG)
U5_BB_CSP: C21.1, R20.2, U5.16 (CS)
U5_BB_VISNS: R11.2, U5.3 (VISNS)
U5_BB_VOSNS: C23.1, R24.2, U5.12 (VOSNS)
U6_DAC_OUT: R26.1, U6.1 (VOUT)
U7_INA_VBUS: R28.2, U7.8 (Vbus)
USB_DM: J1.A7 (D-), J1.B7 (D-), U2.3 (I/O2), U2.4 (I/O2), U4.13 (USB_D-)
USB_DP: J1.A6 (D+), J1.B6 (D+), U2.1 (I/O1), U2.6 (I/O1), U4.14 (USB_D+)
VBUS: C6.1, D1.1 (K), J1.A4 (VBUS), J1.A9 (VBUS), J1.B4 (VBUS), J1.B9 (VBUS), Q1.3 (S), R1.1, R3.1, R8.1, U3.2 (EN), U3.3 (IN)
VGATE: C37.1, D5.1 (K), R29.1, R33.1
VG_IN: C36.1, L3.1, R32.2, U8.4 (EN), U8.5 (IN)
VIN: C5.2, C24.1, C25.1, C26.1, C27.1, C28.1, Q1.2 (D), Q2.5 (D), R2.2, R10.1, R32.1
VOUT: C29.1, C30.1, C31.1, C32.1, C33.1, Q5.5 (D), R17.1, R22.1, R24.1, R27.1
VOUT_SH: Q6.5 (D), R23.1, R27.2, R28.1

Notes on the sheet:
USB-C PD sink (STUSB4500) + VBUS switch
USB data ESD clamp (rail = 3V3)
3.3 V buck (AP63203) from VBUS
ESP32-S3-WROOM-1 (Wi-Fi, native USB)
BOOT button (IO0)
RESET button (EN)
Buck-boost controller (LM5176)
Buck-boost power stage (4 x CSD18563Q5A)
VSET DAC (MCP4725) into FB
Output monitor (INA228 + 10 mOhm shunt)
Output enable (high-side N-FET)
Output terminal + TVS
Rotary encoder + push
OLED header + I2C pull-ups
3V3 power LED
PD contract LED (IO10)
Output-on LED (IO11)
M3 mounting holes
Power flags

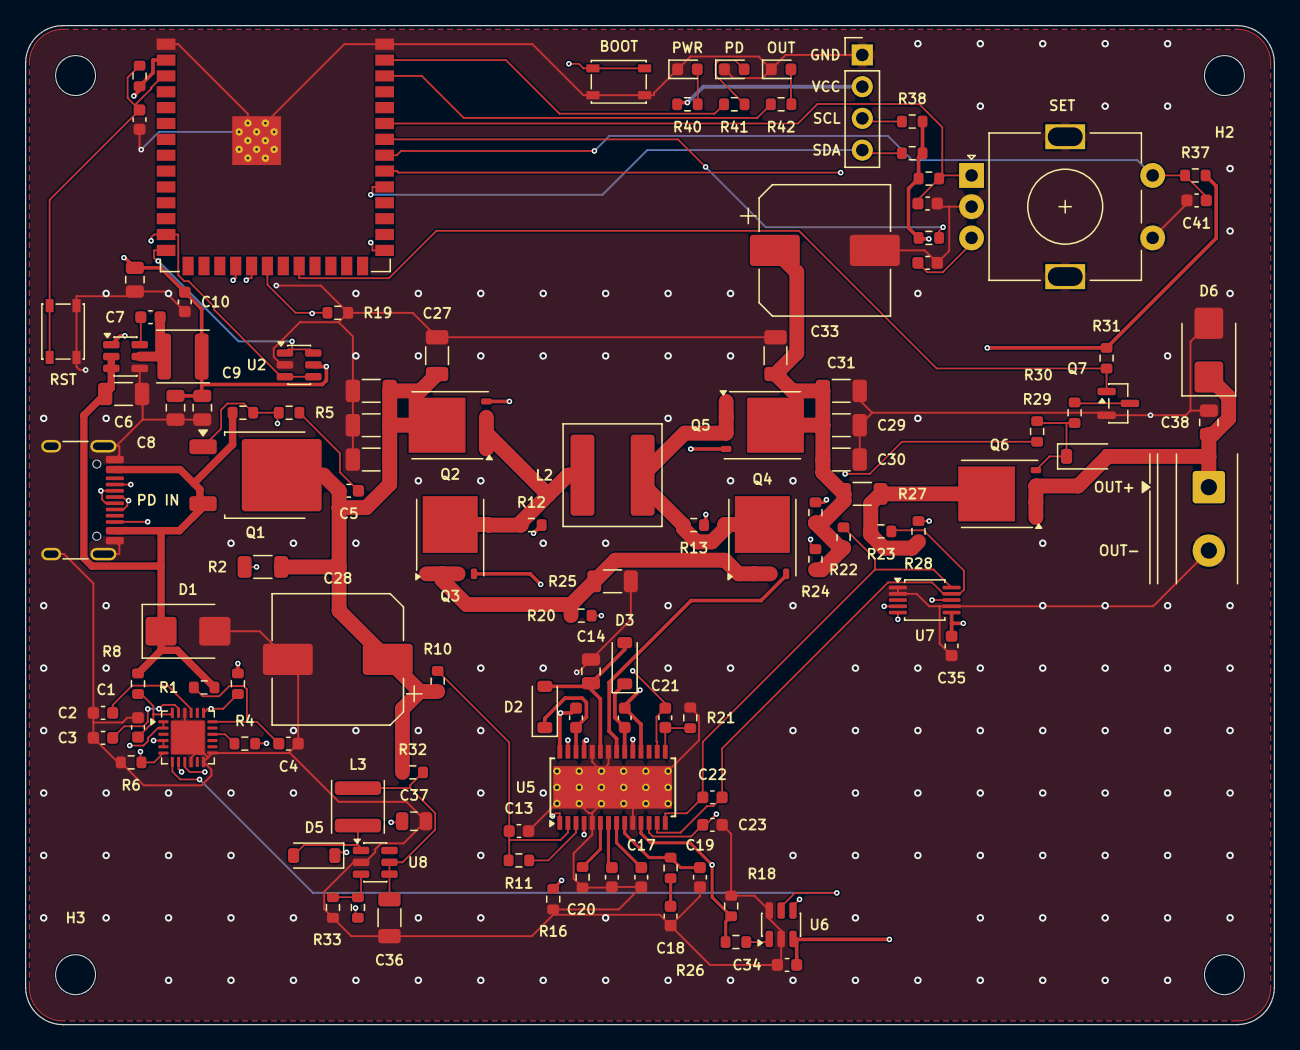
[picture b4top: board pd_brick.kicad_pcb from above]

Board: 4 copper layers, 100.0 x 80.0 mm, 120 parts (0 on the bottom side), 71 nets.

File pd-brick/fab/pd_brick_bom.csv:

"Reference","Value","Footprint","MPN","LCSC","Qty"
"C1,C2,C3,C4,C12,C22","1uF","Capacitor_SMD:C_0603_1608Metric","CL10A105KB8NNNC","C15849","6"
"C5,C7,C10,C13,C15,C16,C34,C35","100nF","Capacitor_SMD:C_0603_1608Metric","CC0603KRX7R9BB104","C14663","8"
"C6,C24,C25,C26,C27,C29,C30,C31,C32","10uF","Capacitor_SMD:C_1206_3216Metric","CL31A106KBHNNNE","C13585","9"
"C8,C9,C11","22uF","Capacitor_SMD:C_0805_2012Metric","CL21A226MAQNNNE","C45783","3"
"C14","4.7uF","Capacitor_SMD:C_0805_2012Metric","CL21A475KAQNNNE","C1779","1"
"C17","33nF","Capacitor_SMD:C_0603_1608Metric","CL10B333KB8NNNC","C21117","1"
"C18,C39,C40,C41","10nF","Capacitor_SMD:C_0603_1608Metric","0603B103K500NT","C57112","4"
"C19,C23","100pF","Capacitor_SMD:C_0603_1608Metric","CL10C101JB8NNNC","C14858","2"
"C20","220pF","Capacitor_SMD:C_0603_1608Metric","CL10B221KB8NNNC","C1603","1"
"C21","47pF","Capacitor_SMD:C_0603_1608Metric","CL10C470JB8NNNC","C1671","1"
"C28,C33","220uF 50V","Capacitor_SMD:CP_Elec_10x10","MA50V220M10x10","C46550473","2"
"C36","4.7uF","Capacitor_SMD:C_1206_3216Metric","1206B475K500NT","C29823","1"
"C37,C38","1uF","Capacitor_SMD:C_0805_2012Metric","CL21B105KBFNNNE","C28323","2"
"D1,D6","SMBJ24A","Diode_SMD:D_SMB","SMBJ24A","C123819","2"
"D2,D3,D5","B5819W","Diode_SMD:D_SOD-123","B5819W SL","C8598","3"
"D4","BZT52C12","Diode_SMD:D_SOD-123","BZT52C12","C173429","1"
"D7","Green (PWR)","LED_SMD:LED_0603_1608Metric","KT-0603G","C12624","1"
"D8","Green (PD)","LED_SMD:LED_0603_1608Metric","KT-0603G","C12624","1"
"D9","Red (OUT)","LED_SMD:LED_0603_1608Metric","KT-0603R","C2286","1"
"J1","USB-C PD","Connector_USB:USB_C_Receptacle_HRO_TYPE-C-31-M-12","TYPE-C-31-M-12","C165948","1"
"J2","OUT","TerminalBlock_Phoenix:TerminalBlock_Phoenix_MKDS-1,5-2-5.08_1x02_P5.08mm_Horizontal","MKDS 1,5/ 2-5,08","C5183929","1"
"J3","OLED","Connector_PinHeader_2.54mm:PinHeader_1x04_P2.54mm_Vertical","PZ254V-11-04P","C2691448","1"
"L1","4.7uH","Inductor_SMD:L_Sunlord_SWPA4030S","SWPA4030S4R7MT","C57269","1"
"L2","4.7uH","Inductor_SMD:L_Coilcraft_XAL7070-XXX","XAL7070-472MEC","C3911513","1"
"L3","22uH","Inductor_SMD:L_Changjiang_FNR4030S","FNR4030S220MT","C167883","1"
"Q1","AOD4185","Package_TO_SOT_SMD:TO-252-2","AOD4185","C400894","1"
"Q2,Q3,Q4,Q5,Q6","CSD18563Q5A","Package_TO_SOT_SMD:TDSON-8-1","CSD18563Q5A","C77239","5"
"Q7","2N7002","Package_TO_SOT_SMD:SOT-23","2N7002","C8545","1"
"R1,R41,R42","1k","Resistor_SMD:R_0603_1608Metric","0603WAF1001T5E","C21190","3"
"R2","1k","Resistor_SMD:R_1206_3216Metric","1206W4F1001T5E","C4410","1"
"R3,R6,R17,R19","100k","Resistor_SMD:R_0603_1608Metric","0603WAF1003T5E","C25803","4"
"R4,R31","22k","Resistor_SMD:R_0603_1608Metric","0603WAF2202T5E","C31850","2"
"R5,R20,R21,R22,R23","100","Resistor_SMD:R_0603_1608Metric","0603WAF1000T5E","C22775","5"
"R7,R18,R30,R35,R36,R37,R38,R39","4.7k","Resistor_SMD:R_0603_1608Metric","0603WAF4701T5E","C23162","8"
"R8,R10,R24,R28,R32","10","Resistor_SMD:R_0603_1608Metric","0603WAF100JT5E","C22859","5"
"R9","10k","Resistor_SMD:R_0603_1608Metric","0603WAF1002T5E","C25804","1"
"R11","2k","Resistor_SMD:R_0603_1608Metric","0603WAF2001T5E","C22975","1"
"R12,R13","1","Resistor_SMD:R_0603_1608Metric","0603WAF100KT5E","C22936","2"
"R14","20k","Resistor_SMD:R_0603_1608Metric","0603WAF2002T5E","C4184","1"
"R15","33k","Resistor_SMD:R_0603_1608Metric","0603WAF3302T5E","C4216","1"
"R16","82k","Resistor_SMD:R_0603_1608Metric","0603WAF8202T5E","C23254","1"
"R25,R27","10m","Resistor_SMD:R_1206_3216Metric","FMF06FTHR010-LH","C105362","2"
"R26","15k","Resistor_SMD:R_0603_1608Metric","0603WAF1502T5E","C22809","1"
"R29,R33","1M","Resistor_SMD:R_0603_1608Metric","0603WAF1004T5E","C22935","2"
"R34","24k","Resistor_SMD:R_0603_1608Metric","0603WAF2402T5E","C23352","1"
"R40","2.2k","Resistor_SMD:R_0603_1608Metric","0603WAF2201T5E","C4190","1"
"SW1","BOOT","Button_Switch_SMD:SW_SPST_PTS810","PTS810SJM250SMTRLFS","C116501","1"
"SW2","RESET","Button_Switch_SMD:SW_SPST_PTS810","PTS810SJM250SMTRLFS","C116501","1"
"SW3","EC11E15244G1","Rotary_Encoder:RotaryEncoder_Alps_EC11E-Switch_Vertical_H20mm","EC11E15244G1","C370970","1"
"U1","STUSB4500QTR","Package_DFN_QFN:QFN-24-1EP_4x4mm_P0.5mm_EP2.7x2.7mm","STUSB4500QTR","C2678061","1"
"U2","USBLC6-2SC6","Package_TO_SOT_SMD:SOT-23-6","USBLC6-2SC6","C7519","1"
"U3","AP63203WU-7","Package_TO_SOT_SMD:TSOT-23-6","AP63203WU-7","C780769","1"
"U4","ESP32-S3-WROOM-1-N8R8","RF_Module:ESP32-S3-WROOM-1","ESP32-S3-WROOM-1-N8R8","C2913201","1"
"U5","LM5176PWPR","Package_SO:HTSSOP-28-1EP_4.4x9.7mm_P0.65mm_EP3.4x9.5mm_ThermalVias","LM5176PWPR","C442493","1"
"U6","MCP4725A0T-E/CH","Package_TO_SOT_SMD:SOT-23-6","MCP4725A0T-E/CH","C144198","1"
"U7","INA228AIDGSR","Package_SO:TSSOP-10_3x3mm_P0.5mm","INA228AIDGSR","C2887910","1"
"U8","MT3608","Package_TO_SOT_SMD:SOT-23-6","MT3608","C84817","1"
